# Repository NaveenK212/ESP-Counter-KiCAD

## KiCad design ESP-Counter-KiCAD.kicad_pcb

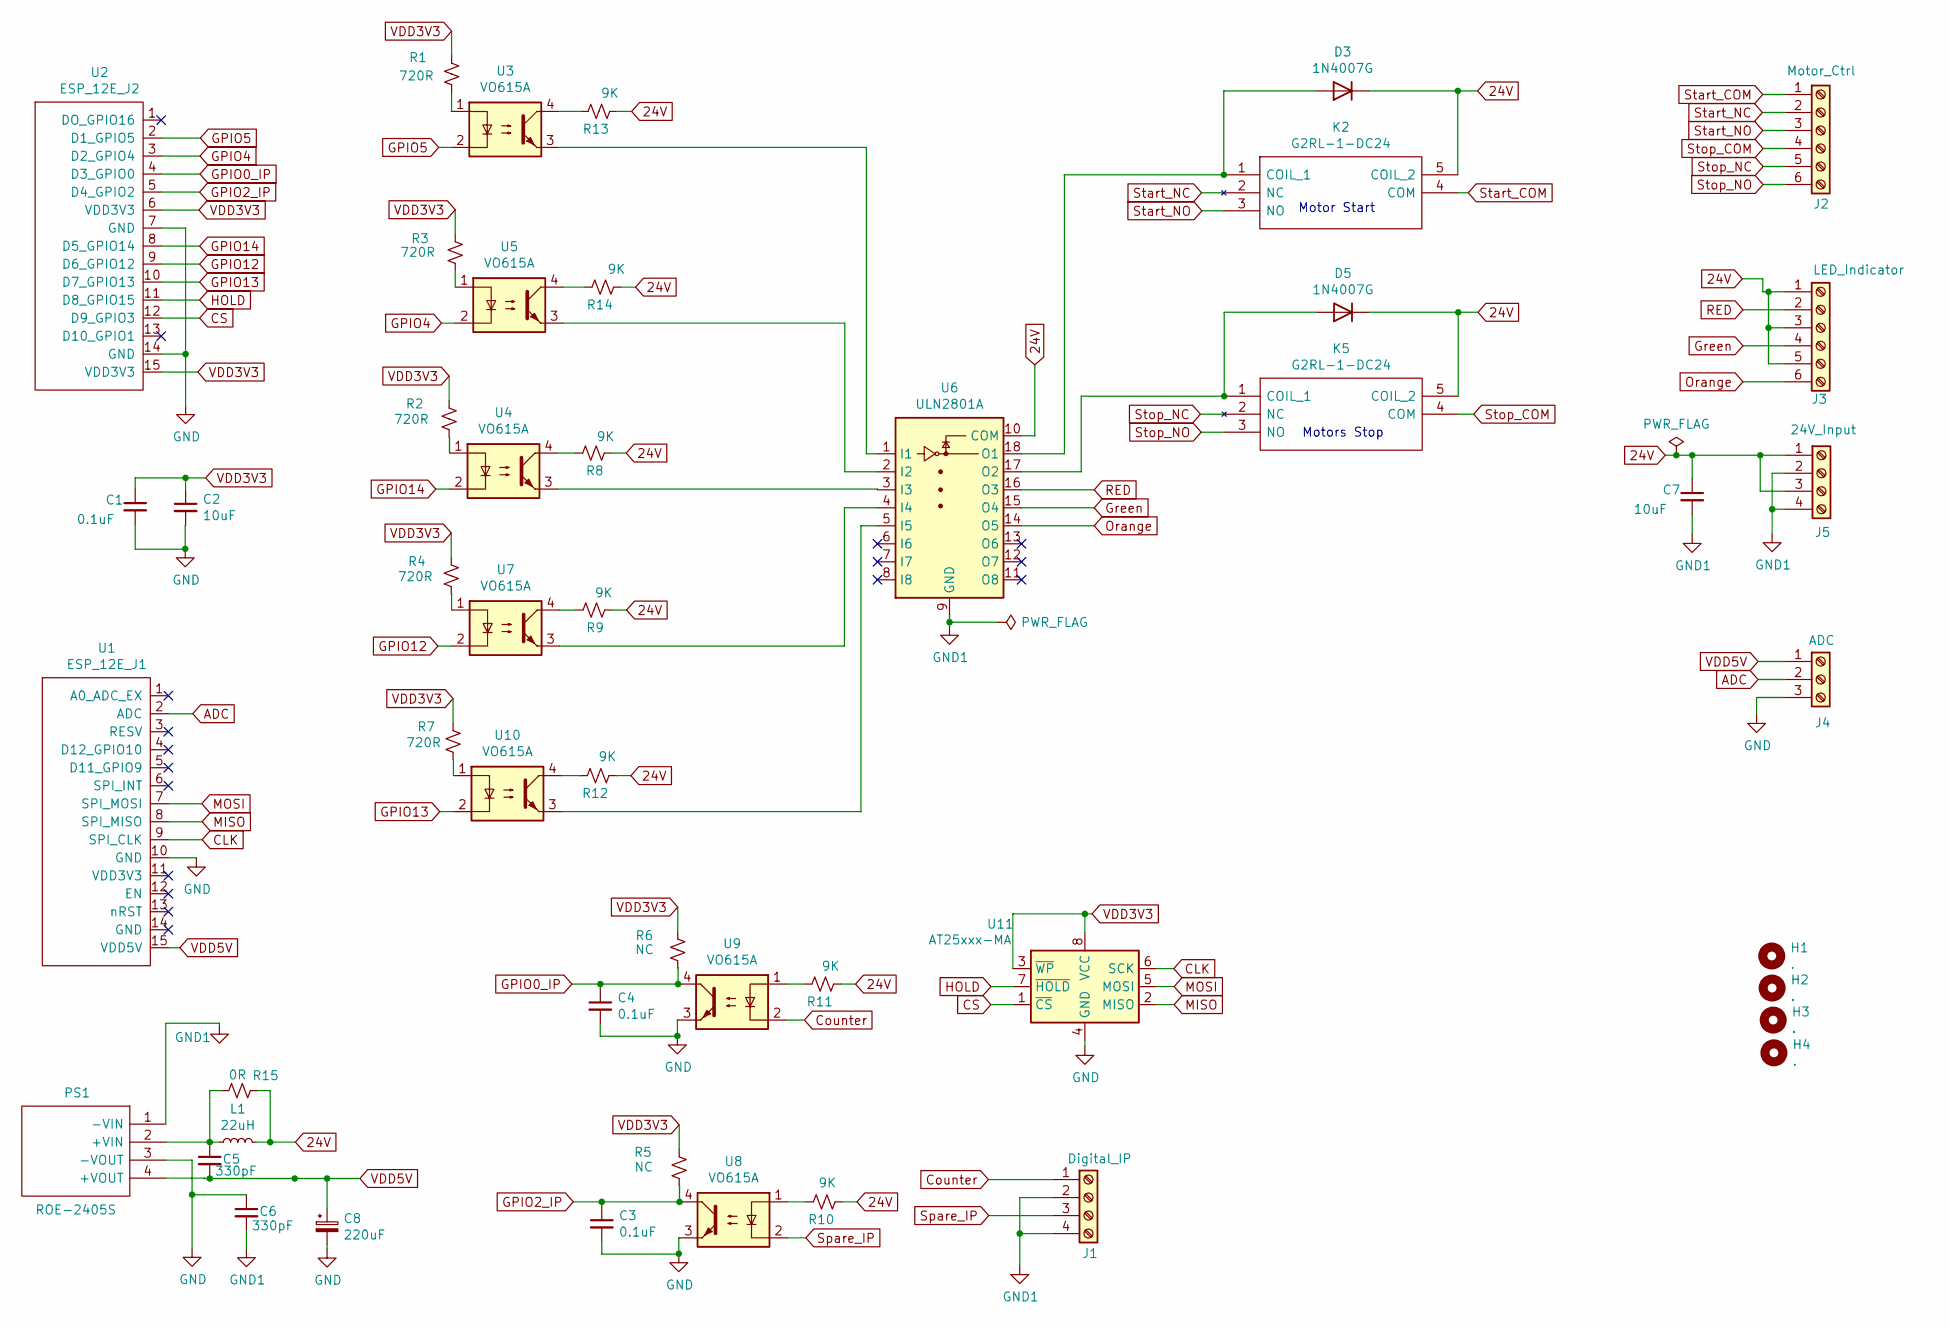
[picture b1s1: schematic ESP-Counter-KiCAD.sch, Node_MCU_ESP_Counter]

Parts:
C1, C3, C4: 0.1uF; C_Disc_D4.3mm_W1.9mm_P5.00mm
C2, C7: 10uF; C_Disc_D4.3mm_W1.9mm_P5.00mm
C5, C6: 330pF; C_Disc_D4.3mm_W1.9mm_P5.00mm
C8: 220uF; CP_Radial_D5.0mm_P2.00mm
D3, D5: 1N4007G; D_DO-41_SOD81_P10.16mm_Horizontal
H1, H2, H3, H4: .; MountingHole_3.2mm_M3
J1: Digital_IP; PinHeader_1x04_P2.54mm_Vertical
J2: Motor_Ctrl; PinHeader_1x06_P2.54mm_Vertical
J3: LED_Indicator; PinHeader_1x06_P2.54mm_Vertical
J4: ADC; PinHeader_1x03_P2.54mm_Vertical
J5: 24V_Input; PinHeader_1x04_P2.54mm_Vertical
K2, K5: G2RL-1-DC24; G2RL14; Manufacturer_Part_Number G2RL-1-DC24; Mouser Part Number 653-G2RL-1-DC24
L1: 22uH; RLS226
PS1: ROE-2405S; ROE1205S; Manufacturer_Part_Number ROE-2405S; Mouser Part Number 919-ROE-2405S
R1, R2, R3, R4, R7: 720R; R_Axial_DIN0309_L9.0mm_D3.2mm_P15.24mm_Horizontal
R5, R6: NC; R_Axial_DIN0309_L9.0mm_D3.2mm_P15.24mm_Horizontal
R8, R9, R10, R11, R12, R13, R14: 9K; R_Axial_DIN0309_L9.0mm_D3.2mm_P15.24mm_Horizontal
R15: 0R; R_Axial_DIN0309_L9.0mm_D3.2mm_P15.24mm_Horizontal
U1: ESP_12E_J1; PinHeader_1x15_P2.54mm_Vertical
U2: ESP_12E_J2; PinHeader_1x15_P2.54mm_Vertical
U3, U4, U5, U7, U8, U9, U10: VO615A; DIP762W60P254L460H455Q4N
U6: ULN2801A; DIP850W46P254L2324H393Q18N
U11: AT25xxx-MA; DFN-8-1EP_3x2mm_P0.5mm_EP1.75x1.45mm

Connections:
24V: C7.1, D3.1 (K), D5.1 (K), J3.1, J3.3, J3.5, J5.1, J5.3, K2.5 (COIL_2), K5.5 (COIL_2), L1.2, R8.2, R9.2, R10.2, R11.2, R12.2, R13.2, R14.2, R15.1, U6.10 (COM)
ADC: J4.2, U1.2 (ADC)
CLK: U1.9 (SPI_CLK), U11.6 (SCK)
CS: U2.12 (D9_GPIO3), U11.1 (~CS)
Counter: J1.1, U9.2
GND: C1.2, C2.2, C3.2, C4.2, C6.1, C8.2, J4.3, PS1.3 (-VOUT), U1.10 (GND), U2.7 (GND), U2.14 (GND), U8.3, U9.3, U11.4 (GND), U11.9 (GND)
GND1: C6.2, C7.2, J1.2, J1.4, J5.2, J5.4, PS1.1 (-VIN), U6.9 (GND)
GPIO0_IP: C4.1, R6.2, U2.4 (D3_GPIO0), U9.4
GPIO2_IP: C3.1, R5.2, U2.5 (D4_GPIO2), U8.4
GPIO4: U2.3 (D2_GPIO4), U5.2
GPIO5: U2.2 (D1_GPIO5), U3.2
GPIO12: U2.9 (D6_GPIO12), U7.2
GPIO13: U2.10 (D7_GPIO13), U10.2
GPIO14: U2.8 (D5_GPIO14), U4.2
Green: J3.4, U6.15 (O4)
HOLD: U2.11 (D8_GPIO15), U11.7 (~HOLD)
MISO: U1.8 (SPI_MISO), U11.2 (MISO)
MOSI: U1.7 (SPI_MOSI), U11.5 (MOSI)
unnamed: C5.1, L1.1, PS1.2 (+VIN), R15.2
unnamed: D3.2 (A), K2.1 (COIL_1), U6.18 (O1)
unnamed: D5.2 (A), K5.1 (COIL_1), U6.17 (O2)
unnamed: R1.2, U3.1
unnamed: R2.2, U4.1
unnamed: R3.2, U5.1
unnamed: R4.2, U7.1
unnamed: R7.2, U10.1
unnamed: R8.1, U4.4
unnamed: R9.1, U7.4
unnamed: R10.1, U8.1
unnamed: R11.1, U9.1
unnamed: R12.1, U10.4
unnamed: R13.1, U3.4
unnamed: R14.1, U5.4
unnamed: U3.3, U6.1 (I1)
unnamed: U4.3, U6.3 (I3)
unnamed: U5.3, U6.2 (I2)
unnamed: U6.4 (I4), U7.3
unnamed: U6.5 (I5), U10.3
Orange: J3.6, U6.14 (O5)
RED: J3.2, U6.16 (O3)
Spare_IP: J1.3, U8.2
Start_COM: J2.1, K2.4 (COM)
Start_NC: J2.2, K2.2 (NC)
Start_NO: J2.3, K2.3 (NO)
Stop_COM: J2.4, K5.4 (COM)
Stop_NC: J2.5, K5.2 (NC)
Stop_NO: J2.6, K5.3 (NO)
VDD3V3: C1.1, C2.1, R1.1, R2.1, R3.1, R4.1, R5.1, R6.1, R7.1, U2.6 (VDD3V3), U2.15 (VDD3V3), U11.3 (~WP), U11.8 (VCC)
VDD5V: C5.2, C8.1, J4.1, PS1.4 (+VOUT), U1.15 (VDD5V)

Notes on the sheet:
Motor Start
Motors Stop

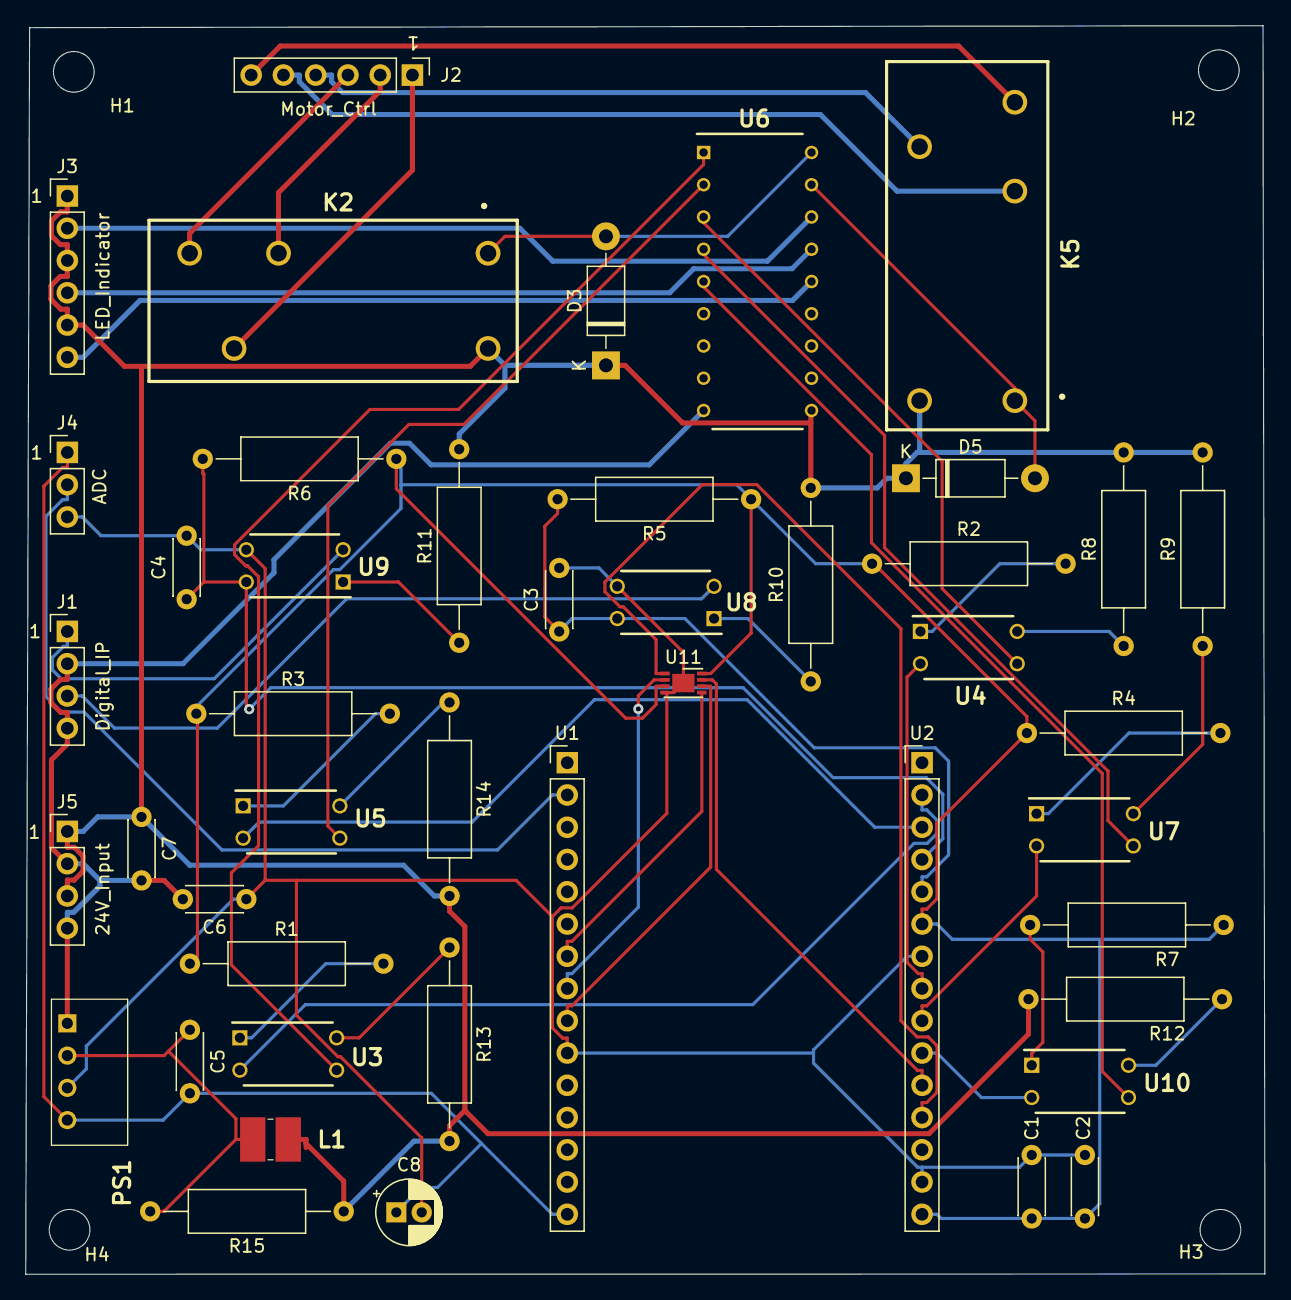
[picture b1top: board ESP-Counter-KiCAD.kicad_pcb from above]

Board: 2 copper layers, 97.6 x 98.3 mm, 49 parts (0 on the bottom side), 49 nets.

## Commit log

2021-02-04 Initial commit - Schematic first verison completed
2021-02-04 Footprint association completed
2021-02-04 DCDC converter symbol added
2021-02-04 Relays for LED & spare removed, driving LED using ULN
2021-02-07 Pullup resisitors values updated
2021-02-11 RECOM DCDC connections completed
2021-02-11 EEPROM added to schematic
2021-02-11 Foot print for inductor added
2021-02-12 First iteration of routing done
2021-02-12 Routing completed - Second iteration
2021-02-12 220uF Cap added at 5V
